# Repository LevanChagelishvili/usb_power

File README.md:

# usb_power
Simple power bank PCB

https://github.com/LevanChagelishvili/usb_power/assets/105656257/3ba233f5-4479-43c8-83bf-6a3f6d8fc1a5

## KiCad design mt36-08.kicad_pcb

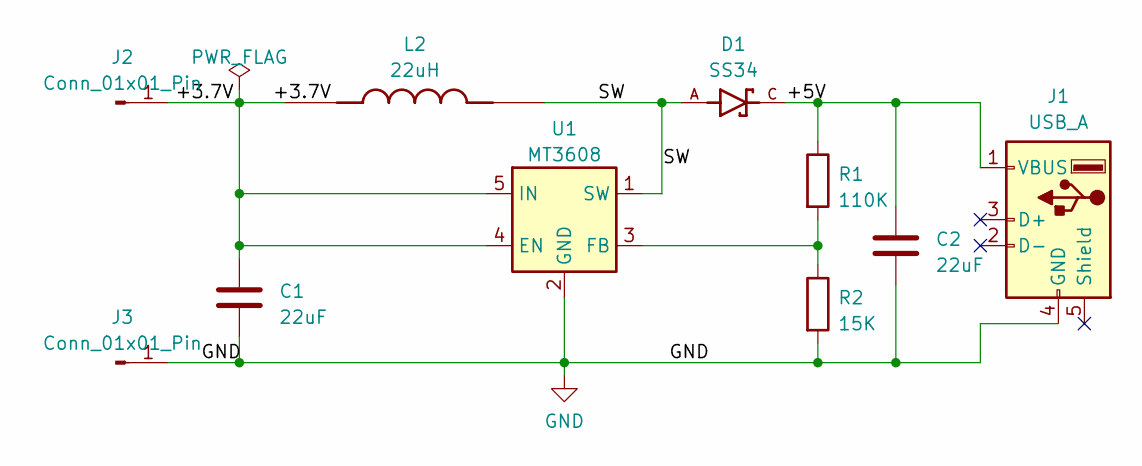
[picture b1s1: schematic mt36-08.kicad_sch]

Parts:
C1, C2: 22uF; C_1206_3216Metric
D1: SS34; DIOM7959X265N; PARTREV 31 Aug 2016
J1: USB_A; USB_A_CONNFLY_DS1095-WNR0
J2, J3: Conn_01x01_Pin; pad
L2: 22uH; L_7.3x7.3_H3.5
R1: 110K; R_0805_2012Metric
R2: 15K; R_0805_2012Metric
U1: MT3608; SOT-23-6

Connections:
/+3.7V: C1.1, J2.1, L2.2, U1.4 (EN), U1.5 (IN)
/+5V: C2.1, D1.C, J1.1 (VBUS), R1.1
/SW: D1.A, L2.1, U1.1 (SW)
GND: C1.2, C2.2, J1.4 (GND), J3.1, R2.2, U1.2 (GND)
unnamed: R1.2, R2.1, U1.3 (FB)

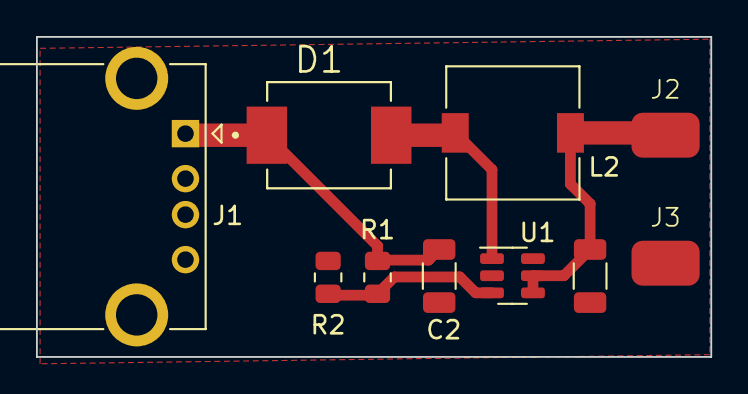
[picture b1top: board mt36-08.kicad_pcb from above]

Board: 2 copper layers, 37.5 x 17.8 mm, 10 parts (0 on the bottom side), 5 nets.

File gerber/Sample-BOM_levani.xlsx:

Comment | Designator | Footprint | JLCPCB Part
22uF | C1 | C_1206_3216Metric | C412630
22uF | C2 | C_1206_3216Metric | C412630
SS34 | D1 | DIOM7959X265N | C2931901
USB_A | J1 | USB_A_CONNFLY_DS1095-WNR0 | C720525
Conn_01x01_Pin | J2 | pad
Conn_01x01_Pin | J3 | pad
22uH | L2 | L_7.3x7.3_H3.5 | C694589
110K | R1 | R_0805_2012Metric | C416064
15K | R2 | R_0805_2012Metric | C416070
MT3608 | U1 | SOT-23-6 | C84817
